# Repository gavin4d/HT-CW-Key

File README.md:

# HT CW Key
This project is a hardware design for an automatic CW (morse) keyer designed to plug straight into a K1 port on a handheld tranceiver.

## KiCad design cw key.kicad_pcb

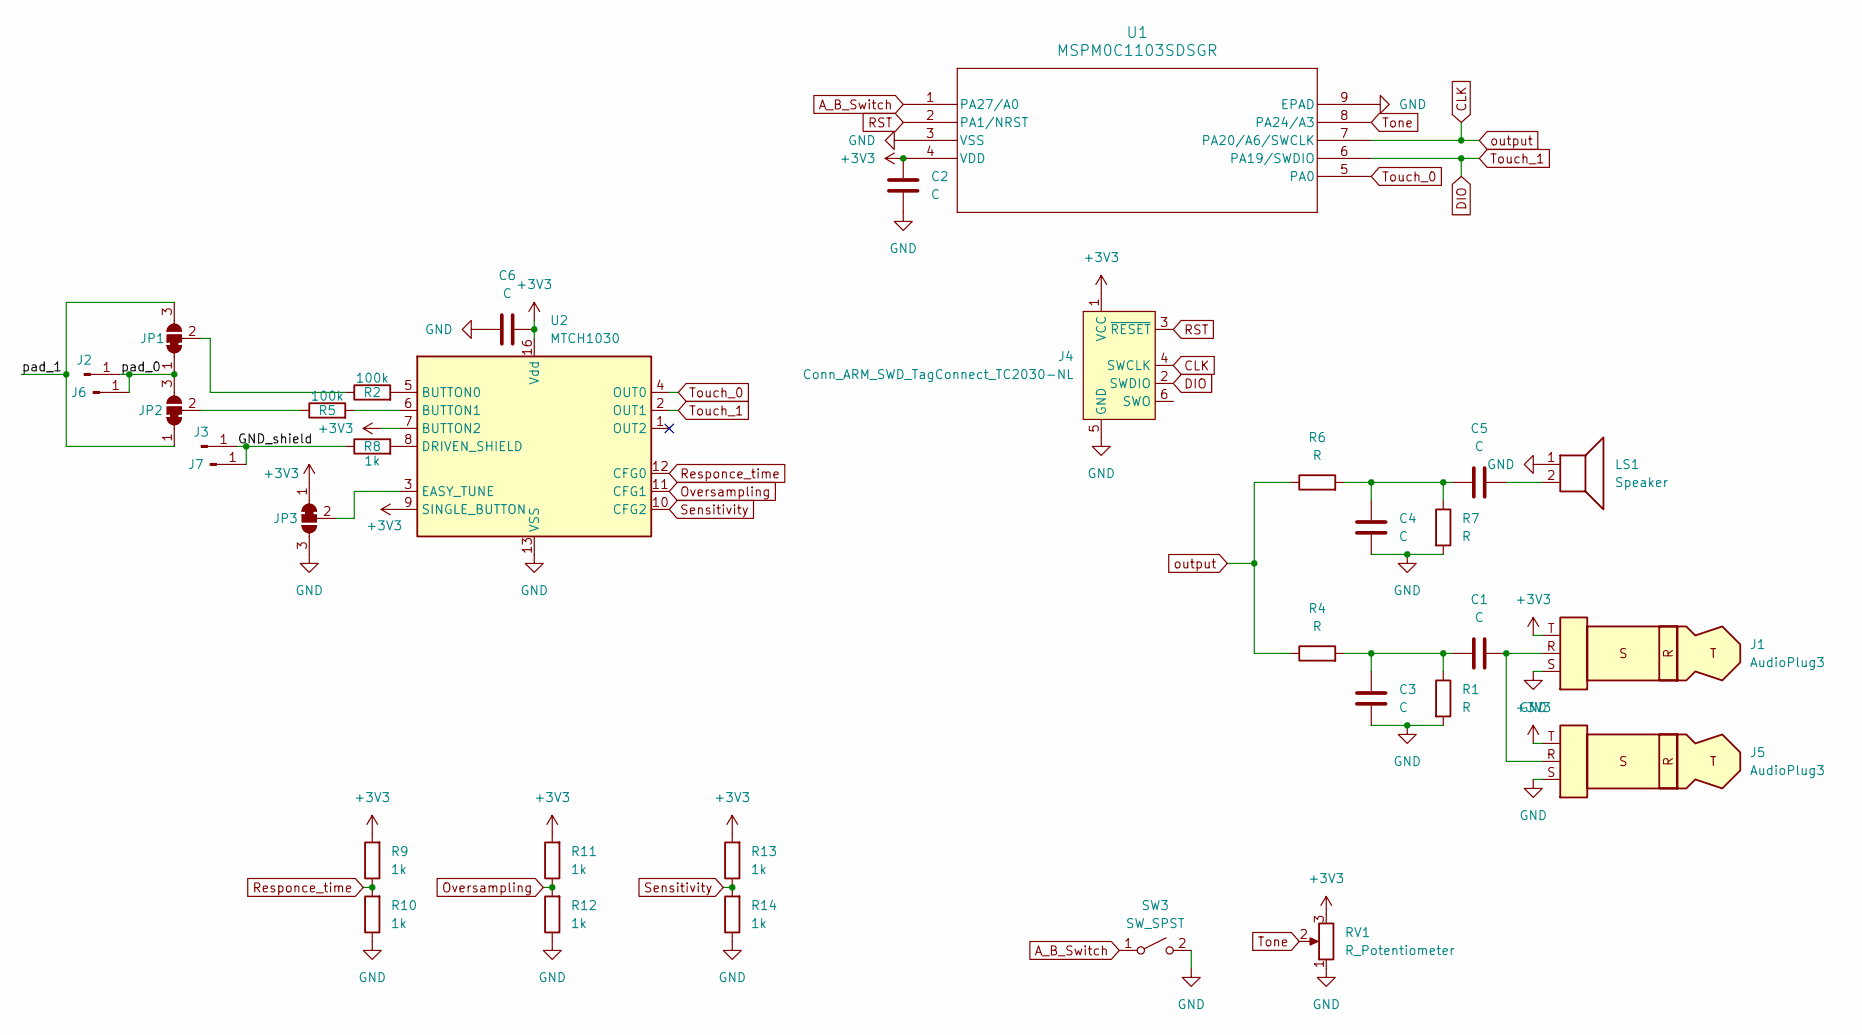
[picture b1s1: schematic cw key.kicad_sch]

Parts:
C1, C2, C3, C4, C5, C6: C; C_0402_1005Metric_Density_C
J1, J5: AudioPlug3; 3.5 mm plug 4 pin
J2, J3, J6, J7: Conn_01x01_Pin; Header_spacer
J4: Conn_ARM_SWD_TagConnect_TC2030-NL; Tag-Connect_TC2030-IDC-NL_2x03_P1.27mm_Vertical
JP1, JP2, JP3: SolderJumper_3_Bridged12; SolderJumper-3_P1.3mm_Bridged12_RoundedPad1.0x1.5mm
LS1: Speaker; OWR-061220LA-32
R1, R4, R6, R7: R; R_0402_1005Metric_Density_C
R2, R5: 100k; R_0402_1005Metric_Density_C
R8, R9, R10, R11, R12, R13, R14: 1k; R_0402_1005Metric_Density_C
RV1: R_Potentiometer; Thumb Pot
SW3: SW_SPST; CFS-0102TA
U1: MSPM0C1103SDSGR; DSG0008A_TEX
U2: MTCH1030; VQFN-16-1EP_3x3mm_P0.5mm_EP1.1x1.1mm

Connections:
+3V3: C2.1, C6.2, J1.T, J4.1 (VCC), J5.T, JP3.1 (A), R9.2, R11.2, R13.2, RV1.3, U1.4 (VDD), U2.7 (BUTTON2), U2.9 (SINGLE_BUTTON), U2.16 (Vdd)
/GND_shield: J3.1, J7.1, R8.1
/pad_0: J2.1, J6.1, JP1.1 (A), JP2.3 (B)
/pad_1: JP1.3 (B), JP2.1 (A)
A_B_Switch: SW3.1 (A), U1.1 (PA27/A0)
CLK: J4.4 (SWCLK), R4.1, R6.1, U1.7 (PA20/A6/SWCLK)
DIO: J4.2 (SWDIO), U1.6 (PA19/SWDIO), U2.2 (OUT1)
GND: C2.2, C3.2, C4.2, C6.1, J1.S, J4.5 (GND), J5.S, JP3.3 (B), LS1.1, R1.2, R7.2, R10.1, R12.1, R14.1, RV1.1, SW3.2 (B), U1.3 (VSS), U1.9 (EPAD), U2.13 (VSS)
unnamed: C1.1, J1.R, J5.R
unnamed: C1.2, C3.1, R1.1, R4.2
unnamed: C4.1, C5.2, R6.2, R7.1
unnamed: C5.1, LS1.2
unnamed: JP1.2 (C), R2.1
unnamed: JP2.2 (C), R5.1
unnamed: JP3.2 (C), U2.3 (EASY_TUNE)
unnamed: R2.2, U2.5 (BUTTON0)
unnamed: R5.2, U2.6 (BUTTON1)
unnamed: R8.2, U2.8 (DRIVEN_SHIELD)
Oversampling: R11.1, R12.2, U2.11 (CFG1)
RST: J4.3 (~RESET), U1.2 (PA1/NRST)
Responce_time: R9.1, R10.2, U2.12 (CFG0)
Sensitivity: R13.1, R14.2, U2.10 (CFG2)
Tone: RV1.2, U1.8 (PA24/A3)
Touch_0: U1.5 (PA0), U2.4 (OUT0)

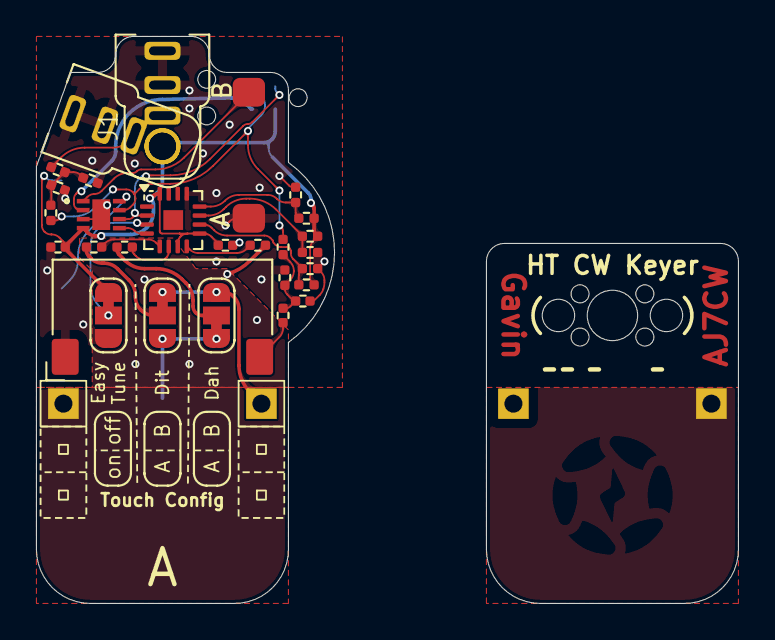
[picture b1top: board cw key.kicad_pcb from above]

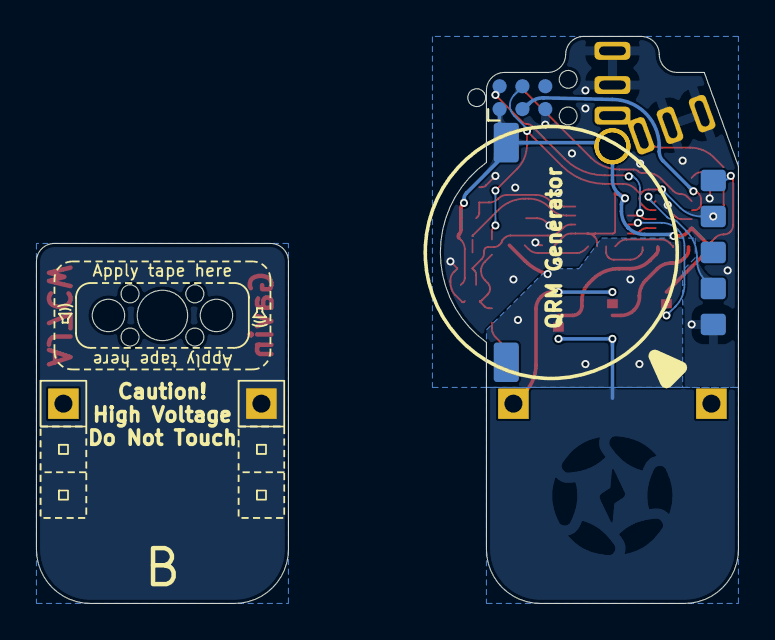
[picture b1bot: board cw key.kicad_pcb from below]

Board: 2 copper layers, 39.0 x 31.5 mm, 34 parts (4 on the bottom side), 24 nets.

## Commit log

2025-08-23 board complete
2025-08-23 removed cw key backups
2025-08-23 updated to use 4 pin 3.5mm jack
2025-08-24 melted
2025-08-24 generated production files
